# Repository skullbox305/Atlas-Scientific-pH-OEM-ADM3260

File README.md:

Eagle PCB Design for Atlas Scientific OEM pH and ORP Sensors. Noise Isolation with ADM3260

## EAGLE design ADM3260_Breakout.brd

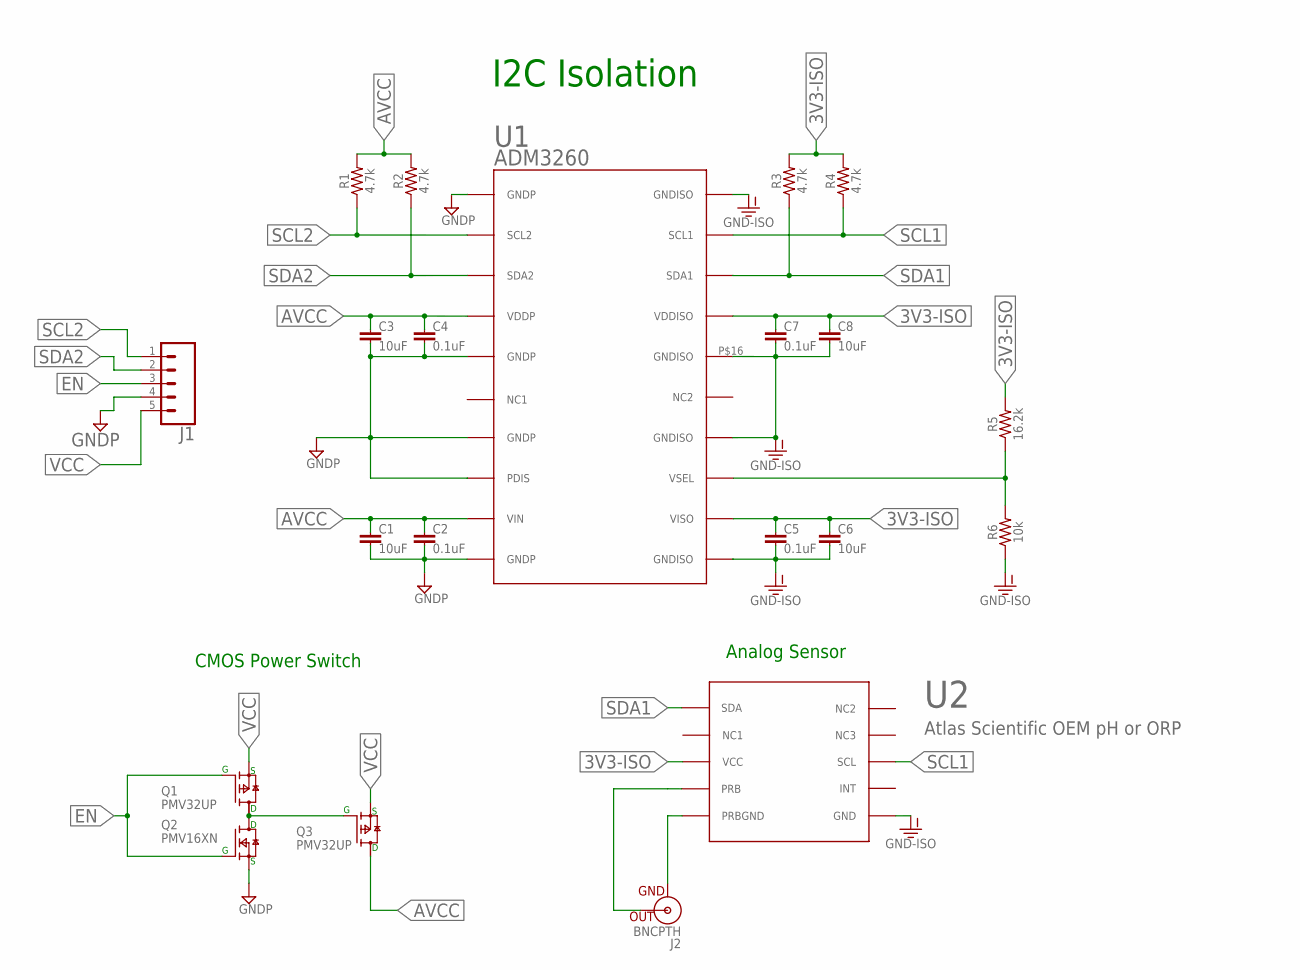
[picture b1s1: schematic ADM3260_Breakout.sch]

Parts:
C1, C3, C6, C8: 10uF; 0805
C2, C4, C5, C7: 0.1uF; 0603
J1: CONN_05LOCK_LONGPADS; 1X05_LOCK_LONGPADS
J2: BNCPTH; BNC
Q1, Q3: PMV32UP; SOT23
Q2: PMV16XN; SOT23
R1, R2, R3, R4: 4.7k; 0603
R5: 16.2k; 0603
R6: 10k; 0603
U1: ADM3260
U2: Atlas Scientific OEM pH or ORP; PHSENSOR

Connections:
3V3-ISO: C5.1, C6.1, C7.1, C8.1, R3.2, R4.2, R5.2, U1.P$12 (VISO), U1.P$17 (VDDISO), U2.P$3 (VCC)
AVCC: C1.1, C2.1, C3.1, C4.1, Q3.3 (D), R1.2, R2.2, U1.P$4 (VDDP), U1.P$9 (VIN)
EN: J1.3, Q1.1 (G), Q2.1 (G)
GND: C1.2, C2.2, C3.2, C4.2, J1.4, Q2.2 (S), U1.P$1 (GNDP), U1.P$5 (GNDP), U1.P$7 (GNDP), U1.P$8 (PDIS), U1.P$10 (GNDP)
GND-ISO: C5.2, C6.2, C7.2, C8.2, R6.1, U1.P$11 (GNDISO), U1.P$14 (GNDISO), U1.P$16 (GNDISO), U1.P$20 (GNDISO), U2.P$6 (GND)
unnamed: R5.1, R6.2, U1.P$13 (VSEL)
unnamed: Q1.3 (D), Q2.3 (D), Q3.1 (G)
PRB: J2.S (OUT), U2.P$4 (PRB)
PRBGND: J2.GND, U2.P$5 (PRBGND)
SCL1: R4.1, U1.P$19 (SCL1), U2.P$8 (SCL)
SCL2: J1.1, R1.1, U1.P$2 (SCL2)
SDA1: R3.1, U1.P$18 (SDA1), U2.P$1 (SDA)
SDA2: J1.2, R2.1, U1.P$3 (SDA2)
VCC: J1.5, Q1.2 (S), Q3.2 (S)

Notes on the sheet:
CMOS Power Switch
I2C Isolation
Analog Sensor

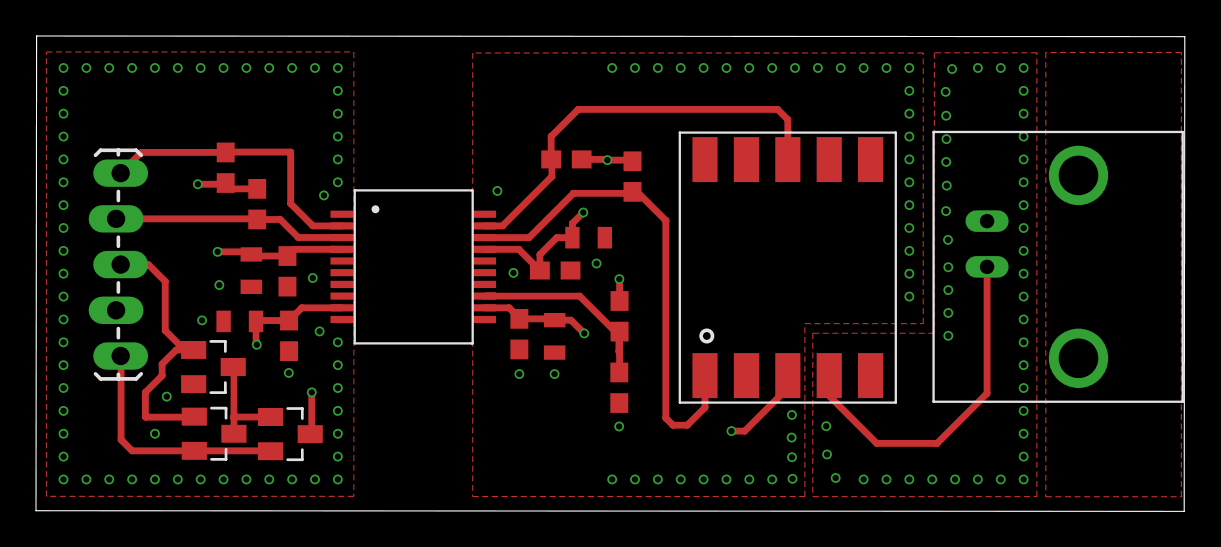
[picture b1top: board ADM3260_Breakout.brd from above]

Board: 4 copper layers, 63.8 x 26.4 mm, 21 parts (0 on the bottom side), 14 nets.

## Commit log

2018-12-05 Added Schematic pdf
2018-12-05 finished, but not checked for errors yet
2018-12-06 uodate
    update

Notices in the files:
parts and their libraries:
SparkFun-Capacitors: Licensing: Creative Commons ShareAlike 4.0 International - https://creativecommons.org/licenses/by-sa/4.0
